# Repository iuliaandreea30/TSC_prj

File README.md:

## TSC Project - E-book-Reader

## Diagram

## BOM (Bill Of Materials)

| Component  | Supplier Link | Datasheet |
|------------|---------------|-----------|
| 112A-TAAR-R03 | [Model](https://store.comet.srl.ro/Catalogue/Product/43497/) | [Datasheet](https://www.snapeda.com/parts/112A-TAAR-R03/Attend/datasheet/) |
| 744043680 | [Model](https://ro.mouser.com/ProductDetail/Wurth-Elektronik/744043680?qs=PGXP4M47uW6VkZq%252BkzjrHA%3D%3D) | [Datasheet](https://www.we-online.com/components/products/datasheet/744043680.pdf) |
| BD5229G-TR | [Model](https://componentsearchengine.com/part-view/BD5229G-TR/ROHM%20Semiconductor) | [Datasheet](https://fscdn.rohm.com/en/products/databook/datasheet/ic/power/voltage_detector/bd52xxg-e.pdf) |
| Capacitor 0402 | [Model](https://ro.mouser.com/c/passive-components/capacitors/ceramic-capacitors/?q=CC0402&srsltid=AfmBOoogjqwwed3xvp6V5-bfVkRuawirfMcnAC47L-UQdC3mnXJk097M) | [Datasheet](https://componentsearchengine.com/Datasheets/2/CC0402MRX5R5BB106.pdf) |
| CPH3225A | [Model](https://www.snapeda.com/parts/CPH3225A/Seiko+Instruments/view-part/?ref=snap) | [Datasheet](https://www.snapeda.com/parts/CPH3225A/Seiko%20Instruments/datasheet/) |
| Custom Button | [Model](https://industry.panasonic.com/global/en/products/control/switch/light-touch/number/evqpuj02k) | [Datasheet](https://industry.panasonic.com/global/en/downloads?tab=catalog&small_g_cd=203&part_no=EVQPUJ02K) |
| DS3231SN | [Model](https://www.snapeda.com/parts/DS3231SN%23/Analog+Devices/view-part/?ref=eda) | [Datasheet](https://www.snapeda.com/parts/DS3231SN%23/Analog%20Devices/datasheet/) |
| ESP32 WROVER 0805 Capacitor | [Model]() | [Datasheet]() |
| ESP32 WROVER BME680 Sensor | [Model](https://www.snapeda.com/parts/BME680/Bosch/view-part/?welcome=home) | [Datasheet](https://www.bosch-sensortec.com/media/boschsensortec/downloads/datasheets/bst-bme680-ds001.pdf) |
| ESP32 WROVER MCP73831 Power Management | [Model](https://www.snapeda.com/parts/BME680/Bosch/view-part/?welcome=home) | [Datasheet](https://www.snapeda.com/parts/MCP73831T-2ACI/OT/Microchip/datasheet/) |
| ESP32C6 Varistor 1812 | [Model]() | [Datasheet]() |
| ESP32C6 WROOM-1-N8| [Model](https://www.snapeda.com/parts/ESP32-C6-WROOM-1-N8/Espressif+Systems/view-part/?ref=eda) | [Datasheet](https://www.snapeda.com/parts/ESP32-C6-WROOM-1-N8/Espressif%20Systems/datasheet/) |
| FH34SRJ-24S-0.5SH | [Model](https://ro.mouser.com/ProductDetail/Hirose-Connector/FH34SRJ-24S-0.5SH99?qs=vcbW%252B4%252BSTIpKBl5ap9J8Fw%3D%3D) | [Datasheet](https://www.snapeda.com/parts/FH34SRJ-24S-0.5SH(99)/Hirose%20Connector/datasheet/) |
| LED Chip 0603 | [Model](https://www.snapeda.com/parts/KP-1608SURCK/Kingbright/view-part/?ref=search&t=LED%200603) | [Datasheet](https://www.snapeda.com/parts/KP-1608SURCK/Kingbright/datasheet/) |
| MAX17048G+T10 | [Model](https://www.snapeda.com/parts/MAX17048G+T10/Analog+Devices/view-part/?ref=eda) | [Datasheet](https://www.snapeda.com/parts/MAX17048G+T10/Analog%20Devices/datasheet/) |
| MBR0530 Schottky Diode | [Model](https://www.snapeda.com/parts/MBR0530/Onsemi/view-part/?ref=snap) | [Datasheet](https://www.snapeda.com/parts/MBR0530/ON%20Semiconductor/datasheet/) |
| PGB1010603MR | [Model](https://www.snapeda.com/parts/PGB1010603MR/Littelfuse/view-part/?ref=eda) | [Datasheet](https://www.snapeda.com/parts/PGB1010603MR/Littelfuse%20Inc./datasheet/) |
| QWIIC Connector | [Model](https://www.snapeda.com/parts/PRT-14417/SparkFun/view-part/) | [Datasheet](https://www.snapeda.com/parts/PRT-14417/SparkFun%20Electronics/datasheet/) |
| RCL CPOL 3528 | [Model](https://www.snapeda.com/parts/CPH3225A/Seiko+Instruments/view-part/?ref=eda) | [Datasheet](https://s3.amazonaws.com/snapeda/datasheet/TAJB475K025RNJ_AVX.pdf) |
| Resistor 0402 | [Model](https://grabcad.com/library/resistor-0402-1) | [Datasheet](https://www.yageo.com/upload/media/product/products/datasheet/rchip/PYu-RC_Group_51_RoHS_L_12.pdf) |
| SI1308EDL-T1-GE3 MOSFET | [Model](https://www.snapeda.com/parts/SI1308EDL-T1-GE3/Vishay+Siliconix/view-part/?welcome=home&ref=eda) | [Datasheet](https://www.snapeda.com/parts/SI1308EDL-T1-GE3/Vishay%20Siliconix/datasheet/) |
| SJ | [Model](https://grabcad.com/library/solder-jumpers-1) | [Datasheet]() |
| USB4110-GF-A | [Model](https://componentsearchengine.com/part-view/USB4110-GF-A/GCT%20(GLOBAL%20CONNECTOR%20TECHNOLOGY)) | [Datasheet](https://gct.co/files/drawings/usb4110.pdf) |
| USBLC6-2SC6Y | [Model](https://www.snapeda.com/parts/USBLC6-2SC6Y/STMicroelectronics/view-part/?welcome=home&ref=eda) | [Datasheet](https://www.snapeda.com/parts/USBLC6-2SC6Y/STMicroelectronics/datasheet/) |
| W25Q512JVEIQ | [Model](https://www.snapeda.com/parts/W25Q512JVEIQ/Winbond+Electronics/view-part/?ref=eda) | [Datasheet](https://www.winbond.com/resource-files/W25Q512JV%20SPI%20RevB%2006252019%20KMS.pdf) |
| XC6220A331MR-G | [Model](https://componentsearchengine.com/part-view/XC6220A331MR-G/Torex) | [Datasheet](https://product.torexsemi.com/system/files/series/xc6220.pdf) |
## Detailed Description of Hardware Features

### 1. Microcontroller – ESP32-C6

- **Processor**: 32-bit RISC-V, up to 160MHz clock speed.

- **Memory**: 512KB internal SRAM and 8MB external flash (W25Q512JVEIQ).

- **Connectivity**: Wi-Fi 6 (802.11ax), Bluetooth 5 (LE), USB 2.0 (full-speed).

- **Peripherals**: SPI, I²C, UART, multiple GPIOs.

- **Power Consumption**: Supports low-power modes (sleep, deep sleep).

---

### 2. Environmental Sensor – BME688

- **Measured Parameters**: Temperature, Humidity, Pressure, and Air Quality (VOC/eCO₂).

- **Interface**: I²C at 400kHz (SDA and SCL).

- **Power Consumption**: Very low (~2.1µA in standby, up to a few mA during active measurement).

---

### 3. E-Paper Display (7.5 inch)

- **Model**: Waveshare (or equivalent) with 800×480 resolution.

- **Interface**: 4-wire SPI + control signals (CS, DC, RST, BUSY).

- **Power Consumption**: Very low in static mode (after refresh); requires higher current during refresh (~15–25mA depending on update mode).

---

### 4. Battery and Power Management

- **Battery**: 2500mAh Li-Po (3.7V nominal).

- **Charging IC**: MCP73831 (Microchip) – Li-Po charging via USB-C (up to 1A).

- **Fuel Gauge**: MAX17048 – monitors charge level, voltage, and battery status (I²C).

- **LDO**: XC6220A331MR-G (example) or equivalent, providing a stable 3.3V to the microcontroller and peripherals.

---

### 5. USB-C Port

- **Function**: Battery charging + Data transfer (USB 2.0 full-speed).

- **Protections**: ESD (USBLC6-2SC6Y) + termination resistors.

- **Possibilities**: Firmware updates via USB (bootloader + external tool) or directly via OTA over Wi-Fi.

---

### 6. Buttons (3x Tactile Switches)

- **Type**: Tactile switch (Panasonic or equivalent).

- **Functions**: Menu navigation, option selection, page turn, etc.

- **Connection**: Each button is connected to an ESP32-C6 GPIO, using a debounce circuit (resistor and capacitor) or debounce handled in firmware.

---

### 7. Qwiic Connector (I²C)

- Standard 4-pin connector: VCC, GND, SDA, SCL.

- Allows easy connection of additional I²C sensors or modules (expansion, testing, fast prototyping).

---

### 8. SD Memory Card Connector (112A-TAAR-R03)

- **Function**: External storage for e-books, logs, or firmware updates.

- **Interface**: Can be configured as SD (1-bit / 4-bit) or SPI, depending on firmware configuration.

---

### 9. RTC – DS3231

- **Function**: Provides accurate real-time clock functionality.

- **Interface**: I²C (shared with BME688 and MAX17048).

- **Backup**: Supercapacitor or secondary battery to maintain timekeeping when main power is off.

---

### 10. Additional Memory

- **W25Q512JVEIQ** (External Flash) – connected to ESP32-C6 via dedicated SPI (quad SPI).

  - Used to store firmware and large data (e.g., e-books).

## Power Consumption Summary
| Component              | Active (mA) | Sleep (mA) | Notes                             |
|-----------------------|-------------|------------|-----------------------------------|
| ESP32-C6          | ~80–100     | ~0.02      | Depends on Wi-Fi & sleep mode     |
| E-Paper Display   | ~26         | ~0.01      | Only during refresh               |
| BME688 Sensor     | ~2.1        | ~0.15      | Sleep mode available              |
| RTC DS3231        | ~0.2        | ~0.2       | Constant low power                |
| MicroSD Card      | ~30–100     | ~0.2       | Depends on access frequency       |
| W25Q512JVEIQ Flash| ~10–20      | ~0.01      | During SPI read/write             |

## ESP32-C6 Pin Mapping

| ESP32-C6 Pin | Component / Signal                  | Why?                                                                  |
|--------------|-------------------------------------|-----------------------------------------------------------------------|
| GPIO1        | I²C SDA (BME688, MAX17048, DS3231, Qwiic) | Shared I²C line – saves pins and allows easy expansion               |
| GPIO2        | I²C SCL (BME688, MAX17048, DS3231, Qwiic) | I²C clock line for all sensors and Qwiic extensions                  |
| GPIO5        | SPI MISO (E-Paper, External Flash)  | Common SPI data input line                                            |
| GPIO6        | SPI MOSI (E-Paper, External Flash)  | Data output line to e-paper and flash                                |
| GPIO7        | SPI CLK                             | Clock signal for the SPI bus                                          |
| GPIO8        | E-Paper CS                          | Selects the display on the SPI bus                                   |
| GPIO9        | E-Paper DC (Data/Command)           | Switches between command and data for the e-paper                    |
| GPIO10       | E-Paper RST                         | Hardware reset for the e-paper display                               |
| GPIO11       | E-Paper BUSY                        | Status pin (busy/free) from the display                              |
| GPIO12       | Button #1                           | Digital input for page forward navigation                            |
| GPIO13       | Button #2                           | Digital input for page backward navigation                           |
| GPIO14       | Button #3                           | Digital input for selection/option                                   |
| GPIO15       | MAX17048 ALERT (optional)           | Low battery level alert pin                                          |
| GPIO16       | USB D+ (internal to USB PHY)        | USB 2.0 line (fixed on ESP32-C6)                                     |
| GPIO17       | USB D- (internal to USB PHY)        | USB 2.0 line (fixed on ESP32-C6)                                     |
| GPIO18       | Status LED (optional)               | Indicator for Wi-Fi activity, charging, notifications                |
| GPIO19       | SD Card CS                          | Chip select for the microSD card (SPI)                               |
| GPIO20       | SD Card MISO                        | Data read from microSD card                                          |
| GPIO21       | SD Card MOSI                        | Data write to microSD card                                           |
| GPIO4        | SD Card CLK                         | Clock signal for the microSD card (SPI)                              |

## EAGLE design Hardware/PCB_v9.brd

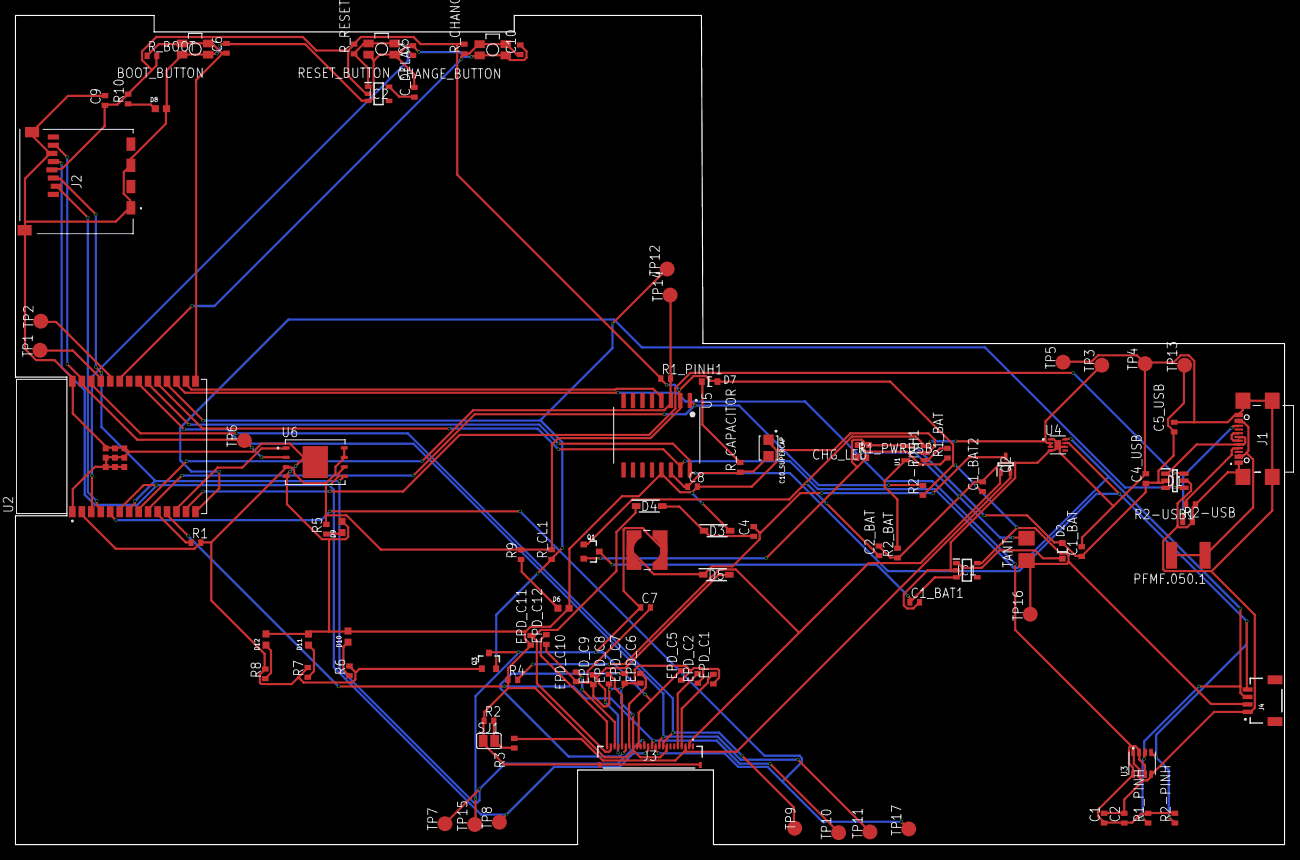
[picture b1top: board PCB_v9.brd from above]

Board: 2 copper layers, 170.2 x 111.2 mm, 103 parts (0 on the bottom side), 61 nets.

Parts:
BOOT_BUTTON: BUTTON_CUSYOMV11; MYBUTTON
C1, C2, C4_USB, C6, C8, C9, C10: 100nF; ESP32_WROVER_EAGLE-LTSPICE_C0402
C1_BAT, C1_BAT1, C1_BAT2, C2_BAT, C5_USB: 4.7uF; ESP32_WROVER_EAGLE-LTSPICE_C0402
C4: 4.7uF/25V; ESP32_WROVER_EAGLE-LTSPICE_C0402
C5: 1uF; ESP32_WROVER_EAGLE-LTSPICE_C0402
C7: 10uF; ESP32_WROVER_EAGLE-LTSPICE_C0402
C10_SUPERCAP: CPH3225A; CAPCP3225X100N
CHANGE_BUTTON: BUTTON_CUSYOMV11; MYBUTTON
CHG_LED: ADAFRUIT_CHIP-LED0603
C_DELAY: 100nF; ESP32_WROVER_EAGLE-LTSPICE_C0402
D1: USBLC6-2SC6Y; SOT95P280X145-6N
D2, D7: ESP32_WROVER_AVX---SD0805S020S1R0_AVX_SD0805S020S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; ESP32_WROVER_AVX---SD0805S020S1R0_AVX_SD0805S020S1R0_0
D3, D4, D5: MBR05301; SOD3716X135N
D6, D8, D9, D10, D11, D12: PGB1010603MR1; DIOC1608X36N
EPD_C1, EPD_C2, EPD_C5, EPD_C6, EPD_C7, EPD_C8, EPD_C9, EPD_C10, EPD_C11, EPD_C12: 1uF/50V; ESP32_WROVER_EAGLE-LTSPICE_C0402
IC1: XC6220A331MR-G; SOT95P280X120-5N
IC2: BD5229G-TR; SOT95P280X125-5N
J1: SAMACSYS_PARTS_USB4110-GF-A; SAMACSYS_PARTS_USB4110GFA
J2: 112A-TAAR-R03_ATTEND; 112ATAARR03ATTEND
J3: FH34SRJ-24S-0.5SH_99_; FH34SRJ24S05SH99
J4: QWIIC_RIGHT_ANGLE; JST04_1MM_RA
L1: 744043680IND_4828-WE-TPC_WRE; IND_4828-WE-TPC_WRE
PFMF.050.1: ESP32C6_VARISTORCN1812; ESP32C6_VARISTOR_CT/CN1812
Q1, Q3: 20V/4.2A/52mΩ/1.4W; ESP32_WROVER_SPARKFUN-DISCRETESEMI_SOT23-3
Q2: SI1308EDL-T1-GE3; SOT65P210X110-3N
R1, R4, R5, R6, R7, R8, R9, R10: 10k; ESP32_WROVER_EAGLE-LTSPICE_R0402
R1_BAT: 200; ESP32_WROVER_EAGLE-LTSPICE_R0402
R1_PINH, R1_PINH1, R2-PINH, R2-PINH1: 10K; ESP32_WROVER_EAGLE-LTSPICE_R0402
R1_PWRUSB: 100k; ESP32_WROVER_EAGLE-LTSPICE_R0402
R2: 2.2; ESP32_WROVER_EAGLE-LTSPICE_R0402
R2-USB, R2-USB1: 5k1; ESP32_WROVER_EAGLE-LTSPICE_R0402
R2_BAT: 2K; ESP32_WROVER_EAGLE-LTSPICE_R0402
R3: 0.47; ESP32_WROVER_EAGLE-LTSPICE_R0402
RESET_BUTTON: BUTTON_CUSYOMV11; MYBUTTON
R_BOOT: 10k; ESP32_WROVER_EAGLE-LTSPICE_R0402
R_CAPACITOR: 15; ESP32_WROVER_EAGLE-LTSPICE_R0402
R_CHANGE: 10k; ESP32_WROVER_EAGLE-LTSPICE_R0402
R_CL1: 10k; ESP32_WROVER_EAGLE-LTSPICE_R0402
R_RESET: 10k; ESP32_WROVER_EAGLE-LTSPICE_R0402
SJ1: SJ
TANT: 100uF; RCL_CT3528
TP1, TP2, TP3, TP4, TP5, TP6, TP7, TP8, TP9, TP10, TP11, TP12, TP13, TP14, TP15, TP16, TP17: TP; TP20R
U1: ESP32_WROVER_SPARKFUN-IC-POWER_MCP73831; ESP32_WROVER_SPARKFUN-IC-POWER_SOT23-5
U2: ESP32-C6-WROOM-1-N8; XCVR_ESP32-C6-WROOM-1-N8
U3: ESP32_WROVER_BME680_BME680; ESP32_WROVER_BME680_PSON80P300X300X100-8N
U4: MAX17048G+T10; SON50P200X200X80-9N
U5: DS3231SN#; SOIC127P1032X265-16N
U6: W25Q512JVEIQ; SON127P600X800X80-9N

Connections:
3V3: C1_BAT2.1, C9.1, D7.2, IC1.5, IC2.2, J2.P4, J4.2, Q3.1, R1.2, R1_PINH1.1, R2-PINH1.1, R5.2, R6.2, R7.2, R8.2, R9.2, R10.2, R_BOOT.2, R_CHANGE.2, R_CL1.2, R_RESET.2, TANT.+, TP16.TP, U2.2, U5.2, U6.3, U6.7, U6.8
32KHZ: R2-PINH1.2, U2.9, U5.1
DN: D1.1, D1.3, J1.A7, J1.B7
DP: J1.A6, J1.B6
EPD_3V3: C7.1, EPD_C5.2, J3.15, J3.16, L1.2, Q3.3, TP15.TP
EPD_3V3_C: Q3.2, R_CL1.1, TP12.TP, U2.18
EPD_BUSY: J3.9, TP9.TP, U2.26
EPD_CS: J3.12, TP10.TP, U2.11
EPD_DC: J3.11, TP17.TP, U2.5
EPD_RST: J3.10, TP11.TP, U2.21
FLASH_CS: U2.12, U6.1
GDR: J3.2, Q2.1, R4.2
GND: BOOT_BUTTON.1, BOOT_BUTTON.2, C1.2, C1_BAT.2, C1_BAT1.2, C1_BAT2.2, C2.2, C2_BAT.2, C4_USB.2, C5.2, C5_USB.2, C6.2, C7.2, C8.2, C9.2, C10.2, C10_SUPERCAP.1, CHANGE_BUTTON.1, CHANGE_BUTTON.2, C_DELAY.2, D1.5, D3.2, D6.2, D8.2, D9.2, D10.2, D11.2, D12.2, EPD_C1.1, EPD_C2.1, EPD_C5.1, EPD_C6.1, EPD_C7.1, EPD_C8.1, EPD_C9.1, EPD_C10.1, EPD_C11.1, EPD_C12.1, IC1.2, IC2.3, J1.A1, J1.A12, J1.B1, J1.B12, J1.MP1, J1.MP2, J1.MP3, J1.MP4, J2.G1, J2.G2, J2.G3, J2.G4, J2.P6, J3.8, J3.17, J3.MP1, J3.MP2, J4.1, R1_PWRUSB.1, R2.1, R2-USB.2, R2-USB1.1, R2_BAT.1, R4.1, RESET_BUTTON.1, RESET_BUTTON.2, SJ1.1, TANT.-, TP4.TP, TP5.TP, U1.2, U2.1, U2.28, U2.29_1, U2.29_2, U2.29_3, U2.29_4, U2.29_5, U2.29_6, U2.29_7, U2.29_8, U2.29_9, U3.1, U3.5, U3.7, U4.1, U4.4, U4.6, U4.9, U5.13, U6.4, U6.9
GPIO8: R1.1, U2.10
I2C_PW: C1.1, C2.1, R1_PINH.2, R2-PINH.2, U2.17, U3.2, U3.6, U3.8
INT_RTC: R1_PINH1.2, TP14.TP, U2.8, U5.3
IO/BOOT: BOOT_BUTTON.3, BOOT_BUTTON.4, C6.1, R_BOOT.1, U2.15
IO/CHANGE: C10.1, CHANGE_BUTTON.3, CHANGE_BUTTON.4, R_CHANGE.1, U2.23
MISO: J2.P7, TP6.TP, U2.27, U6.2
MOSI: J2.P3, J3.14, TP7.TP, U2.7, U6.5
unnamed: C1_BAT1.1, D2.1, IC1.1, IC1.3, Q1.3
unnamed: C4.1, D3.1, D4.2
unnamed: J1.A5, R2-USB1.2
unnamed: R1_BAT.2, U1.1
unnamed: R2_BAT.2, U1.5
unnamed: EPD_C6.2, J3.18
unnamed: EPD_C8.2, J3.20
unnamed: J1.B5, R2-USB.1
unnamed: CHG_LED.C, R1_BAT.1
unnamed: EPD_C1.2, J3.4
unnamed: EPD_C2.2, J3.5
unnamed: EPD_C7.2, J3.19
unnamed: EPD_C10.2, J3.22
unnamed: D7.1, R_CAPACITOR.2
unnamed: EPD_C12.2, J3.24
unnamed: D12.1, R8.1
unnamed: C_DELAY.1, IC2.5
unnamed: D11.1, R7.1
unnamed: D10.1, R6.1
unnamed: D9.1, R5.1
unnamed: D6.1, R9.1
unnamed: D8.1, R10.1
PREVGH: D5.2, EPD_C9.2, J3.21
PREVGL: D4.1, EPD_C11.2, J3.23
RESE: J3.3, Q2.2, R3.2
RESE': R2.2, R3.1, SJ1.2
RESET: C5.1, IC2.1, RESET_BUTTON.3, RESET_BUTTON.4, R_RESET.1, U2.3
RTC_RST: U2.16, U5.4
RX: TP2.TP, U2.24
SCK: J2.P5, J3.13, TP8.TP, U2.6, U6.6
SCL: J4.4, R2-PINH.1, U2.20, U3.4, U4.7, U5.16
SDA: J4.3, R1_PINH.1, U2.19, U3.3, U4.8, U5.15
SRC: C4.2, D5.1, L1.1, Q2.3
SS_SD: J2.P2, U2.4
TX: TP1.TP, U2.25
USB_D+: D1.4, U2.14
USB_D-: D1.6, U2.13
VBAT: C2_BAT.1, Q1.1, TP3.TP, U1.3, U4.2, U4.3
VBUS: C1_BAT.1, C4_USB.1, C5_USB.1, CHG_LED.A, D1.2, D2.2, Q1.2, R1_PWRUSB.2, TP13.TP, U1.4
VRTC: C8.1, C10_SUPERCAP.2, R_CAPACITOR.1, U5.14
VUSB: J1.A4, J1.A9, J1.B4, J1.B9, PFMF.050.1.1, PFMF.050.1.2

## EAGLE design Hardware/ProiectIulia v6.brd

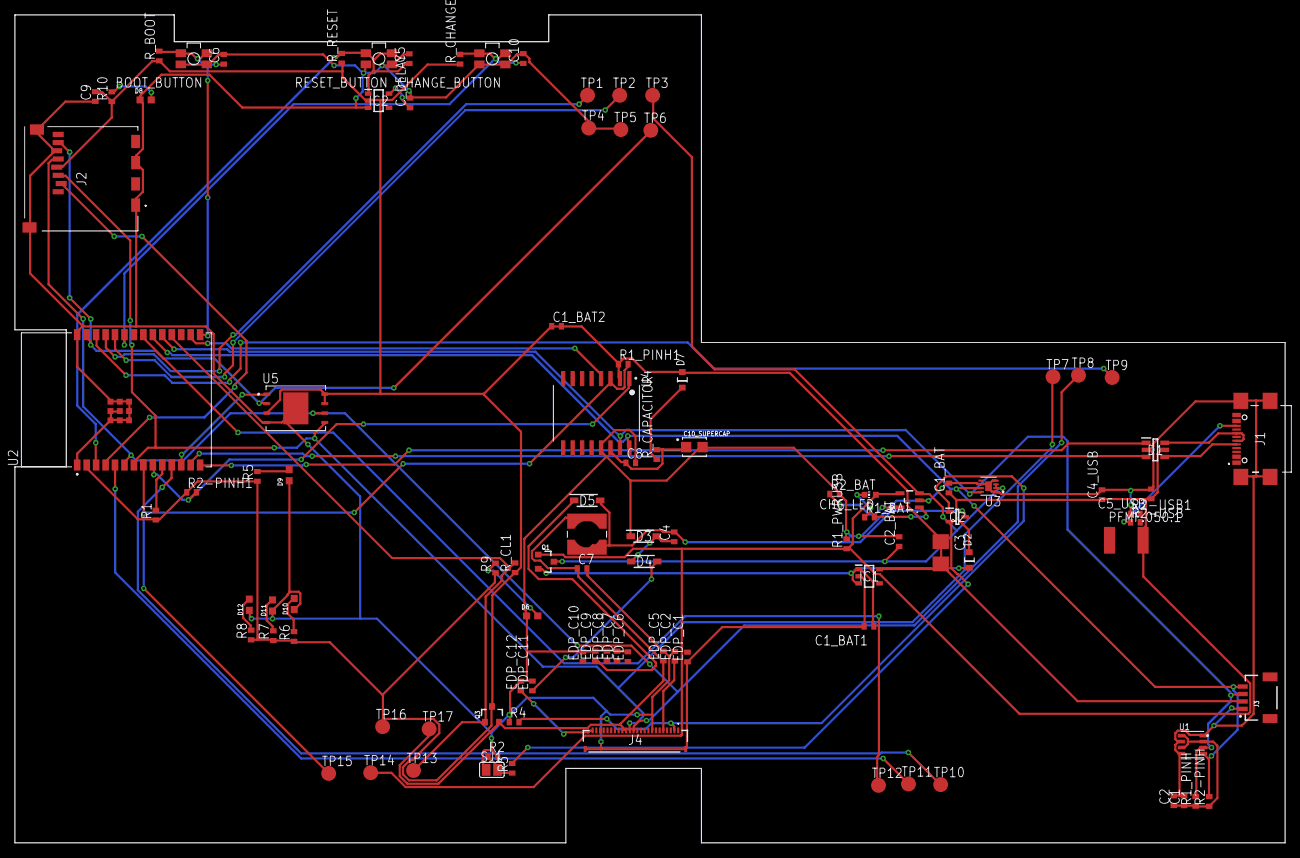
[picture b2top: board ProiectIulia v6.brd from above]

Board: 2 copper layers, 170.6 x 111.2 mm, 103 parts (0 on the bottom side), 61 nets.

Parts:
BOOT_BUTTON: BUTTON_CUSYOMV1; MYBUTTON
C1, C1_BAT1, C1_BAT2, C5_USB: 4.7uF; EAGLE-LTSPICE_C0402
C1_BAT, C2_BAT: 4.7uF; ESP32_WROVER_EAGLE-LTSPICE_C0402
C2, C4_USB, C6, C8, C9, C10: 100nF; EAGLE-LTSPICE_C0402
C3: 100uF TANT; RCL_CT3528
C4: 4.7uF/25V; ESP32_WROVER_EAGLE-LTSPICE_C0402
C5: 1uF; EAGLE-LTSPICE_C0402
C7: 10uF; ESP32_WROVER_EAGLE-LTSPICE_C0402
C10_SUPERCAP: CPH3225A; CAPCP3225X100N
CHANGE_BUTTON: BUTTON_CUSYOMV1; MYBUTTON
CHG_LED: ADAFRUIT_CHIP-LED0603
C_DELAY: 100nF; EAGLE-LTSPICE_C0402
D1: USBLC6-2SC6Y; SOT95P280X145-6N
D2, D7: ESP32_WROVER_AVX---SD0805S020S1R0_AVX_SD0805S020S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; ESP32_WROVER_AVX---SD0805S020S1R0_AVX_SD0805S020S1R0_0
D3, D4, D5: MBR0530; SOD3716X135N
D6, D8, D9, D10, D11, D12: PGB1010603MR; DIOC1608X36N
EDP_C1, EDP_C2: 1uF/50V; EAGLE-LTSPICE_C0402
EDP_C5, EDP_C6, EDP_C7, EDP_C8, EDP_C9, EDP_C10, EDP_C11, EDP_C12: 0.1uF/50V; EAGLE-LTSPICE_C0402
IC1: XC6220A331MR-G; SOT95P280X120-5N
IC2: BD5229G-TR; SOT95P280X125-5N
J1: SAMACSYS_PARTS_USB4110-GF-A; SAMACSYS_PARTS_USB4110GFA
J2: 112A-TAAR-R03_ATTEND; 112ATAARR03ATTEND
J3: QWIIC_RIGHT_ANGLE; JST04_1MM_RA
J4: FH34SRJ-24S-0.5SH_99_; FH34SRJ24S05SH99
L1: 744043680IND_4828-WE-TPC_WRE; IND_4828-WE-TPC_WRE
PFMF.050.1: ESP32C6_VARISTORCN1812; ESP32C6_VARISTOR_CT/CN1812
Q1, Q3: 20V/4.2A/52mΩ/1.4W; ESP32_WROVER_SPARKFUN-DISCRETESEMI_SOT23-3
Q2: SI1308EDL-T1-GE3; SOT65P210X110-3N
R1, R1_PINH, R1_PINH1, R2-PINH, R2-PINH1, R4, R5, R6, R7, R8, R9, R10: 10K; ESP32_WROVER_EAGLE-LTSPICE_R0402
R1_BAT: 200; ESP32_WROVER_EAGLE-LTSPICE_R0402
R1_PWRUSB: 100K; ESP32_WROVER_EAGLE-LTSPICE_R0402
R2: 2.2; ESP32_WROVER_EAGLE-LTSPICE_R0402
R2-USB, R2-USB1: 5k1; ESP32_WROVER_EAGLE-LTSPICE_R0402
R2_BAT: 2K; ESP32_WROVER_EAGLE-LTSPICE_R0402
R3: 0.47; ESP32_WROVER_EAGLE-LTSPICE_R0402
RESET_BUTTON: BUTTON_CUSYOMV1; MYBUTTON
R_BOOT: 10K; ESP32_WROVER_EAGLE-LTSPICE_R0402
R_CAPACITOR: 15K; ESP32_WROVER_EAGLE-LTSPICE_R0402
R_CHANGE: 10K; ESP32_WROVER_EAGLE-LTSPICE_R0402
R_CL1: 10K; ESP32_WROVER_EAGLE-LTSPICE_R0402
R_RESET: 10K; ESP32_WROVER_EAGLE-LTSPICE_R0402
SJ1: SJ
TP1, TP2, TP3, TP4, TP5, TP6, TP7, TP8, TP9, TP10, TP11, TP12, TP13, TP14, TP15, TP16, TP17: TPTP20R; TP20R
U1: ESP32_WROVER_BME680_BME680; ESP32_WROVER_BME680_PSON80P300X300X100-8N
U2: ESP32-C6-WROOM-1-N8; XCVR_ESP32-C6-WROOM-1-N8
U3: MAX17048G+T10; SON50P200X200X80-9N
U4: DS3231SN#; SOIC127P1032X265-16N
U5: W25Q512JVEIQ; SON127P600X800X80-9N
U6: ESP32_WROVER_SPARKFUN-IC-POWER_MCP73831; ESP32_WROVER_SPARKFUN-IC-POWER_SOT23-5

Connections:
3V3: C1_BAT2.1, C1_BAT2.2, C3.+, C3.-, C9.2, D7.2, IC1.5, IC2.2, J2.P4, J3.2, Q3.3, R1.1, R1_PINH1.1, R2-PINH1.1, R5.1, R6.1, R7.1, R8.1, R9.1, R10.1, R_BOOT.1, R_CHANGE.1, R_CL1.1, R_RESET.1, TP16.TP, U2.2, U4.2, U5.3, U5.7, U5.8
32KHZ: R2-PINH1.2, U2.9, U4.1
DN: D1.4, J1.A7, J1.B7
DP: D1.6, J1.A6, J1.B6
EPD_3V3: C7.1, EDP_C5.1, J4.15, J4.16, L1.2, Q3.2, TP17.TP
EPD_3V3_C: Q3.1, R_CL1.2, TP13.TP, U2.18
EPD_BUSY: TP9.TP, U2.26
EPD_CS: TP10.TP, U2.11
EPD_DC: TP11.TP, U2.5
EPD_RST: TP12.TP, U2.21
FLASH_CS: U2.12, U5.1
GDR: J4.2, Q2.1, R4.2
GND: BOOT_BUTTON.1, BOOT_BUTTON.2, C1.2, C1_BAT.2, C1_BAT1.2, C2.2, C2_BAT.2, C4_USB.2, C5.2, C5_USB.2, C6.2, C7.2, C8.2, C9.1, C10.2, C10_SUPERCAP.2, CHANGE_BUTTON.1, CHANGE_BUTTON.2, C_DELAY.2, D1.2, D3.1, D6.1, D8.1, D9.1, D10.1, D11.1, D12.1, EDP_C1.1, EDP_C2.2, EDP_C5.2, EDP_C6.2, EDP_C7.2, EDP_C8.2, EDP_C9.2, EDP_C10.2, EDP_C11.2, EDP_C12.2, IC1.2, IC2.3, J1.A1, J1.A12, J1.B1, J1.B12, J1.MP1, J1.MP2, J1.MP3, J1.MP4, J2.G1, J2.G2, J2.G3, J2.G4, J2.P6, J3.1, J4.8, J4.17, J4.MP1, J4.MP2, R1_PWRUSB.2, R2.2, R2-USB.2, R2-USB1.1, R2_BAT.2, R4.1, RESET_BUTTON.1, RESET_BUTTON.2, SJ1.1, TP4.TP, TP5.TP, U1.1, U1.5, U1.7, U2.1, U2.28, U2.29_1, U2.29_2, U2.29_3, U2.29_4, U2.29_5, U2.29_6, U2.29_7, U2.29_8, U2.29_9, U3.1, U3.4, U3.6, U3.9, U4.13, U5.4, U5.9, U6.2
GPI08: R1.2, U2.10
I2C_PW: C1.1, C2.1, R1_PINH.1, R2-PINH.1, U1.2, U1.6, U1.8
INT_RTC: R1_PINH1.2, TP15.TP, U2.8, U4.3
IO/BOOT: BOOT_BUTTON.3, BOOT_BUTTON.4, C6.1, R_BOOT.2, U2.15
IO/CHANGE: C10.1, CHANGE_BUTTON.3, CHANGE_BUTTON.4, R_CHANGE.2, U2.23
MISO: J2.P7, TP6.TP, U2.27, U5.2
MOSI: J2.P3, J4.14, TP7.TP, U2.7, U5.5
unnamed: EDP_C6.1, J4.18
unnamed: C1_BAT1.1, D2.1, IC1.1, IC1.3, Q1.2
unnamed: J1.A5, R2-USB1.2
unnamed: EDP_C7.1, J4.19
unnamed: EDP_C1.2, J4.4
unnamed: EDP_C2.1, J4.5
unnamed: EDP_C8.1, J4.20
unnamed: C_DELAY.1, IC2.5
unnamed: EDP_C12.1, J4.24
unnamed: D7.1, R_CAPACITOR.1
unnamed: J1.B5, R2-USB.1
unnamed: EDP_C10.1, J4.22
unnamed: D12.2, R8.2
unnamed: D11.2, R7.2
unnamed: D10.2, R6.2
unnamed: D9.2, R5.2
unnamed: D6.2, R9.2
unnamed: D8.2, R10.2
unnamed: R1_BAT.2, U6.1
unnamed: CHG_LED.C, R1_BAT.1
unnamed: R2_BAT.1, U6.5
unnamed: C4.1, D3.2, D4.1
PREVGH: D5.1, EDP_C9.1, J4.21
PREVGL: D4.2, EDP_C11.1, J4.23
RESE: J4.3, Q2.2, R3.2
RESE': R2.1, R3.1, SJ1.2
RESET: C5.1, IC2.1, RESET_BUTTON.3, RESET_BUTTON.4, R_RESET.2, U2.3
RTC_RST: U2.16, U4.4
RX: TP2.TP, U2.24
SCK: J2.P5, J4.13, TP8.TP, U2.6, U5.6
SCL: J3.4, R2-PINH.2, U1.4, U2.20, U3.7, U4.16
SDA: J3.3, R1_PINH.2, U1.3, U2.19, U3.8, U4.15
SRC: C4.2, D5.2, L1.1, Q2.3
SS_SD: J2.P2, U2.4
TX: TP1.TP, U2.25
USB_D+: D1.1, U2.14
USB_D-: D1.3, U2.13
VBAT: C2_BAT.1, Q1.3, TP3.TP, U3.2, U3.3, U6.3
VBUS: C1_BAT.1, C4_USB.1, C5_USB.1, CHG_LED.A, D1.5, D2.2, PFMF.050.1.2, Q1.1, R1_PWRUSB.1, TP14.TP, U6.4
VRTC: C8.1, C10_SUPERCAP.1, R_CAPACITOR.2, U4.14
VUSB: J1.A4, J1.A9, J1.B4, J1.B9, PFMF.050.1.1

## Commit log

2025-04-06 Create LICENSE

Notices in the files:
parts and their libraries:
COPYRIGHT: Copyright (C) 2024 Ultra Librarian. All rights reserved.
